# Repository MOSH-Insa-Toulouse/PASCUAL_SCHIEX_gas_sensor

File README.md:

# LoRa/TTN connected gas sensor
Realised by Alvaro PASCUAL & Quentin SCHIEX for the **Microcontroller and Open-Source Hardware project** at INSA Toulouse/_5ISS_
## Description
We have created a LoRa connected gas sensor during the TPs done at Microcontrollers and open source hardware. For this, we have used an Arduino UNO and a RN2483 LoRa chip, as well as a gas sensor designed with the help of the AIME. Then we designed an electronic circuit to connect each element together using KiCAD. Finally, we developed the software to be flashed to the arduino UNO. It get the sensor value and send it using LoRa.

## arduino_connected_gas_sensor
In this directory is the code we have developed to monitor the gas sensor and use the chip LoRa to send a message when the sensor detects gas. It is only needed to start the program when everything is connected and it will work propertly (you will only need to change the LoRa authent fields).

## DemoShield
In this directory is the PCB we designed using KiCAD. We have used an Arduino UNO template to design a shield that can easily be connected to an arduino UNO. It is composed of the gas sensor, the RN2483 LoRa breakout and an amplification stage. Once that the PCB is printed, you will have to solder components to it and plug the RN2483 breakout using the corresponding pins.

## How to use
To use this project, you will need to
- Get an Arduino UNO, the AIME gas sensor, an LTC1050 amp, an RN2483 breakout, some resistors and capacitors as presented at  the third part of Jean-Louis NOULLET website http://sourcecode.fr/insa/ISS/Smart_Device_Analog_Part.html
- Print the PCB
- Solder everything as shown in KiCad schematics and Part 3 of http://sourcecode.fr/insa/ISS/Smart_Device_Analog_Part.html
- Modify the .ino file LoRa authent values according to your LoRa app
- Flash the arduino with the .ino file
- Connect the shield and the arduino together

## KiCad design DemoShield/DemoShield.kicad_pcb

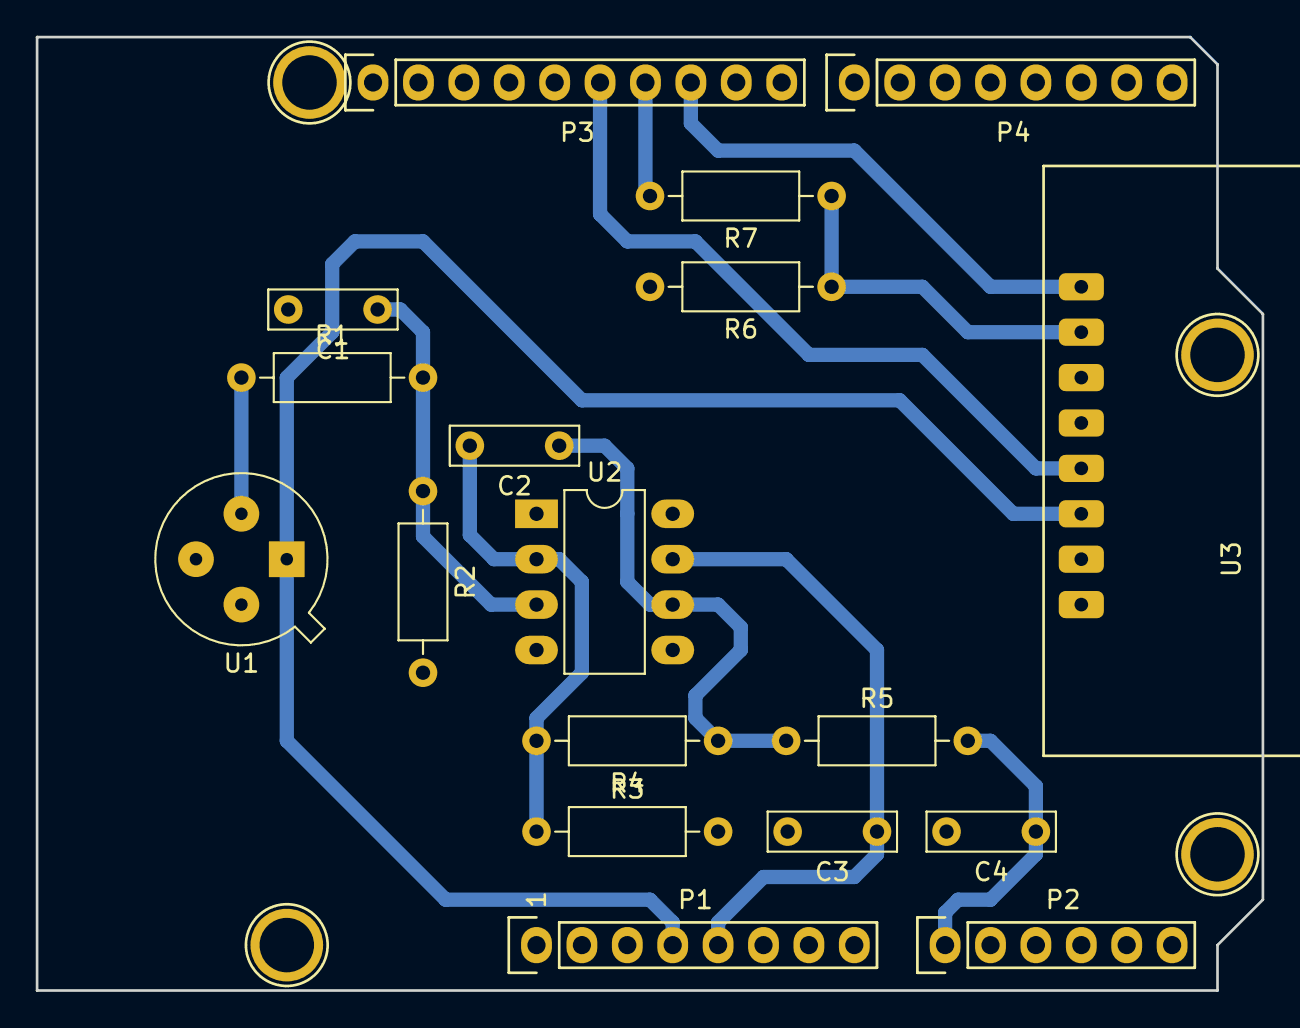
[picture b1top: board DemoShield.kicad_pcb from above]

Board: 2 copper layers, 68.6 x 53.3 mm, 22 parts (0 on the bottom side), 12 nets.

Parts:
C1, C2, C3, C4: C; C_Rect_L7.0mm_W2.0mm_P5.00mm
P1: Power; Socket_Strip_Arduino_1x08
P2: Analog; Socket_Strip_Arduino_1x06
P3: Digital; Socket_Strip_Arduino_1x10
P4: Digital; Socket_Strip_Arduino_1x08
P5, P6, P7, P8: CONN_01X01; Arduino_1pin
R1, R2, R3, R4, R5, R6, R7: R; R_Axial_DIN0207_L6.3mm_D2.5mm_P10.16mm_Horizontal
U1: gas_sensor; myTO-5-4
U2: LTC1050; DIP-8_W7.62mm_LongPads
U3: RN2483Breakout; RN2483 Breakout

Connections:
+3V3: P1.4, U1.1, U3.6
+5V: C3.1, P1.5, U2.7
/10(**/SS): P3.8, U3.1
/11(**/MOSI): P3.7, R7.2
/12(MISO): P3.6, U3.5
/A0: C4.1, P2.1, R5.2
GND: C1.2, C3.2, C4.2, P1.6, P1.7, P3.4, R2.2, R3.2, R6.2, U2.4, U3.8
unnamed: C1.1, R1.2, R2.1, U2.3
unnamed: C2.1, R4.1, R5.1, U2.6
unnamed: C2.2, R3.1, R4.2, U2.2
unnamed: R1.1, U1.2
unnamed: R6.1, R7.1, U3.2

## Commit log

2018-11-28 board V1
2018-11-29 shield V2
2018-11-29 Code V1
